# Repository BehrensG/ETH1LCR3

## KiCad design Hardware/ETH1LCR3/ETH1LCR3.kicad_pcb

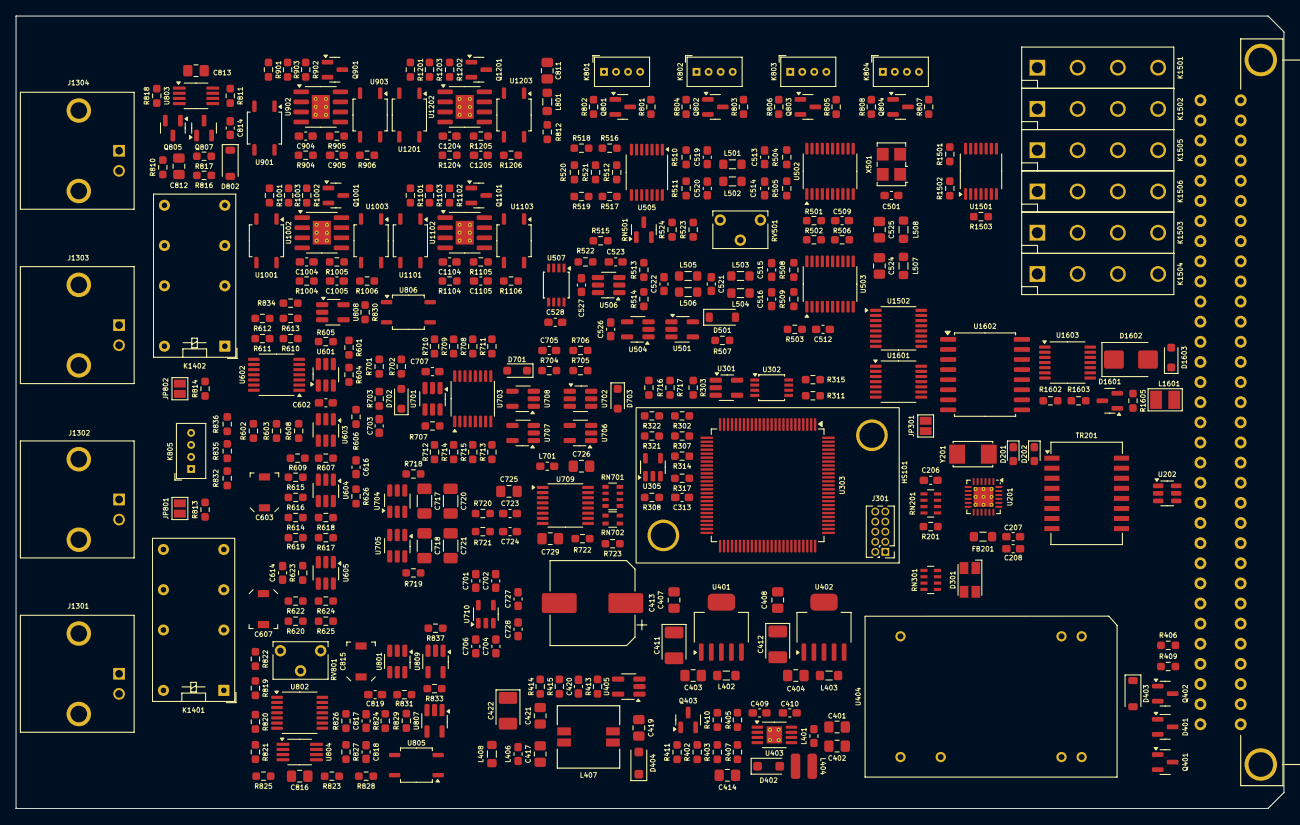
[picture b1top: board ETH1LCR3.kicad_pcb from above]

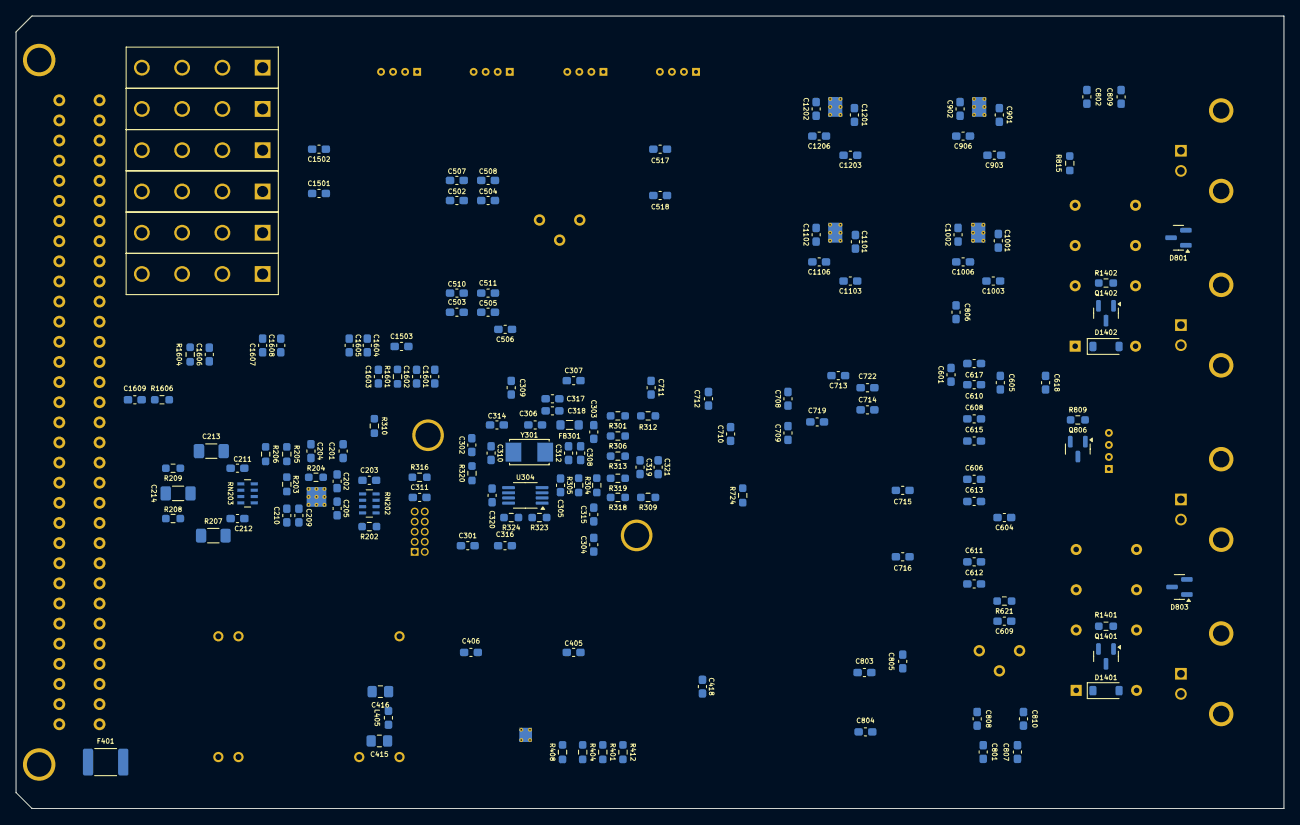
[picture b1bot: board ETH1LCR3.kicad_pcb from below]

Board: 4 copper layers, 160.0 x 100.0 mm, 534 parts (158 on the bottom side), 378 nets, no tracks yet.

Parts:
C201, C204, C310, C312: 8p; C_0603_1608Metric_Pad1.08x0.95mm_HandSolder
C202, C208, C209, C210, C211, C212, C301, C302, C303, C304, C306, C307, C308, C309, C311, C313, C318, C320, C321, C410, C501, C502, C503, C506, C507, C508, C509, C510, C511, C512, C517, C518, C526, C527, C528, C605, C606, C608, C610, C611, C612, C613, C615, C617, C618, C701, C704, C705, C708, C709, C710, C712, C713, C714, C715, C716, C719, C722, C728, C801, C802, C803, C804, C805, C806, C807, C808, C809, C810, C901, C902, C1001, C1002, C1101, C1102, C1201, C1202, C1501, C1502, C1601, C1603, C1604, C1606, C1608: 0.1u; C_0603_1608Metric_Pad1.08x0.95mm_HandSolder
C203: 470p; C_0603_1608Metric_Pad1.08x0.95mm_HandSolder
C205, C206, C207, C314, C319, C418, C702, C703, C706, C727, C1503, C1602, C1605, C1607: 1u; C_0603_1608Metric_Pad1.08x0.95mm_HandSolder
C213, C214: 1n/1kV; C_1206_3216Metric_Pad1.33x1.80mm_HandSolder
C305: 100n; C_0603_1608Metric_Pad1.08x0.95mm_HandSolder
C315, C316: 2u2; C_0603_1608Metric_Pad1.08x0.95mm_HandSolder
C317: 10u; C_0603_1608Metric_Pad1.08x0.95mm_HandSolder
C401, C414, C415, C417, C421, C524, C525, C725, C726, C729, C812, C813, C816: 4u7; C_0805_2012Metric_Pad1.18x1.45mm_HandSolder
C402, C403, C404, C407, C408, C416: 2u2; C_0805_2012Metric_Pad1.18x1.45mm_HandSolder
C405, C406, C504, C505, C814, C819: 10n; C_0603_1608Metric_Pad1.08x0.95mm_HandSolder
C409: 270p; C_0603_1608Metric_Pad1.08x0.95mm_HandSolder
C411, C412, C422: 33u/12V; CP_EIA-3528-21_Kemet-B_Pad1.50x2.35mm_HandSolder
C413: 470u/12V; CP_Elec_10x10.5
C419: 1u; C_0805_2012Metric_Pad1.18x1.45mm_HandSolder
C420: 1n; C_0603_1608Metric_Pad1.08x0.95mm_HandSolder
C513, C514, C519, C520: 220p; C_0603_1608Metric_Pad1.08x0.95mm_HandSolder
C515, C516, C616: 82p; C_0603_1608Metric_Pad1.08x0.95mm_HandSolder
C521: 68p; C_0603_1608Metric_Pad1.08x0.95mm_HandSolder
C522, C601, C1609: 47p; C_0603_1608Metric_Pad1.08x0.95mm_HandSolder
C523, C604, C906, C1006, C1106, C1206: 1p5; C_0603_1608Metric_Pad1.08x0.95mm_HandSolder
C602, C903, C1003, C1103: DNP; C_0603_1608Metric_Pad1.08x0.95mm_HandSolder
C603, C607: JZ200; C_Trimmer_Voltronics_JZ
C609: 240p; C_0603_1608Metric_Pad1.08x0.95mm_HandSolder
C614, C707, C905, C1005, C1105, C1205: 22p; C_0603_1608Metric_Pad1.08x0.95mm_HandSolder
C711: 100p; C_0603_1608Metric_Pad1.08x0.95mm_HandSolder
C717, C718, C720, C721: 100n/C0G; C_1206_3216Metric_Pad1.33x1.80mm_HandSolder
C723, C724: 15p/C0G; C_0603_1608Metric_Pad1.08x0.95mm_HandSolder
C811: DNP; C_0805_2012Metric_Pad1.18x1.45mm_HandSolder
C815: JZ100; C_Trimmer_Voltronics_JZ
C817: 6p8; C_0603_1608Metric_Pad1.08x0.95mm_HandSolder
C818: 180p; C_0603_1608Metric_Pad1.08x0.95mm_HandSolder
C904, C1004, C1104, C1204: 3p9; C_0603_1608Metric_Pad1.08x0.95mm_HandSolder
C1203: 1p; C_0603_1608Metric_Pad1.08x0.95mm_HandSolder
D201: YELLOW; LED_0603_1608Metric_Pad1.05x0.95mm_HandSolder
D202: GREEN; LED_0603_1608Metric_Pad1.05x0.95mm_HandSolder
D301: ASMB-MTB1-0B3A2; LED_Avago_PLCC4_3.2x2.8mm_CW
D401: BZX84C10LT1G; SOT-23
D402, D404: MBR0520; D_SOD-123F
D403, D501, D802, D1401, D1402: 1N4148W; D_SOD-123
D701, D702, D703: NSVRB751V40T1G; D_SOD-323_HandSoldering
D801, D803: BAV199; SOT-23
D1601: BAV99; SOT-23
D1602: SMBJ5.0A; D_SMB
D1603: SD36C-01FTG; D_SOD-323_HandSoldering
F401: 1812L075/33DR; Fuse_1812_4532Metric_Pad1.30x3.40mm_HandSolder
FB201, FB301: 742792031; L_0805_2012Metric_Pad1.05x1.20mm_HandSolder
HS101: Heatsink; 960-19-12-S-AB-0
J301: 20021111-00010T4LF; PinHeader_2x05_P1.27mm_Vertical
J1301, J1302, J1303, J1304: 5227161-1; TE_5227161-1
J1501: DIN41612_02x32_AC; Socket_DIN41612-CaseC1-AC-Male-64Pin-2rows
JP301, JP801, JP802: Open; SolderJumper-2_P1.3mm_Open_Pad1.0x1.5mm
K801, K802, K803, K804, K805: UMS05-1A80-75D; Relay_StandexMeder_UMS
K1401, K1402: G5V-2-DC5; Relay_DPDT_Omron_G5V-2
K1501, K1502, K1503, K1504, K1505, K1506: HE3621A0510; HE360_x-5050462-8
L401, L405, L406, L701: MLZ1608DR47DT; L_0603_1608Metric_Pad1.05x0.95mm_HandSolder
L402, L403, L408, L507, L508: MLZ2012M100WT; L_0805_2012Metric_Pad1.05x1.20mm_HandSolder
L404: SRN3010TA-2R2M; SRN3010TA
L407: DRQ73-220-R; DRQ73
L501, L502, L503, L504, L505, L506: MLZ2012M330WT; L_0805_2012Metric_Pad1.05x1.20mm_HandSolder
L801: DNP; L_0805_2012Metric_Pad1.05x1.20mm_HandSolder
L1601: CW252016-R33G; CW252016
Q401: SI5618A; SOT-23
Q402, Q801, Q802, Q803, Q804, Q806, Q1401, Q1402: MMBT3904; SOT-23
Q403, Q901, Q1001, Q1101, Q1201: BSS123; SOT-23
Q805, Q807: BFR106; SOT-23
R201, R204, R310, R316, R403, R404, R407, R414, R802, R804, R806, R808, R809, R902, R1002, R1102, R1202, R1401, R1402, R1601: 10k; R_0603_1608Metric_Pad0.98x0.95mm_HandSolder
R202, R315, R704: 1k5; R_0603_1608Metric_Pad0.98x0.95mm_HandSolder
R203: 12k1; R_0603_1608Metric_Pad0.98x0.95mm_HandSolder
R205, R206, R901, R1001, R1101, R1201: 560; R_0603_1608Metric_Pad0.98x0.95mm_HandSolder
R207: 1M/1kV; R_1206_3216Metric_Pad1.30x1.75mm_HandSolder
R208, R209: 75/1%; R_0603_1608Metric_Pad0.98x0.95mm_HandSolder
R301, R705, R720, R721: 3k; R_0603_1608Metric_Pad0.98x0.95mm_HandSolder
R302, R606, R707: 2k; R_0603_1608Metric_Pad0.98x0.95mm_HandSolder
R303, R401, R402, R412, R522, R602, R603, R614, R626, R722, R833, R834, R837, R905, R906, R1005, R1006, R1105, R1106, R1205, R1206, R1501, R1502: 51; R_0603_1608Metric_Pad0.98x0.95mm_HandSolder
R304, R309: 110k; R_0603_1608Metric_Pad0.98x0.95mm_HandSolder
R305, R308, R406, R409, R411, R523, R723, R724, R813, R814, R818, R823, R824, R827, R831: 100k; R_0603_1608Metric_Pad0.98x0.95mm_HandSolder
R306: 3k6; R_0603_1608Metric_Pad0.98x0.95mm_HandSolder
R307, R716, R717: 1k6; R_0603_1608Metric_Pad0.98x0.95mm_HandSolder
R311, R507, R811, R829, R830, R1503, R1604: 1k; R_0603_1608Metric_Pad0.98x0.95mm_HandSolder
R312, R1605: 47; R_0603_1608Metric_Pad0.98x0.95mm_HandSolder
R313: 56k; R_0603_1608Metric_Pad0.98x0.95mm_HandSolder
R314: 160k; R_0603_1608Metric_Pad0.98x0.95mm_HandSolder
R317, R318, R323, R324, R501, R506, R512: 4k7; R_0603_1608Metric_Pad0.98x0.95mm_HandSolder
R319, R320, R321, R322: 0; R_0603_1608Metric_Pad0.98x0.95mm_HandSolder
R405: 27k; R_0603_1608Metric_Pad0.98x0.95mm_HandSolder
R408: 2k4; R_0603_1608Metric_Pad0.98x0.95mm_HandSolder
R410, R706: 12k; R_0603_1608Metric_Pad0.98x0.95mm_HandSolder
R413, R415: 30k; R_0603_1608Metric_Pad0.98x0.95mm_HandSolder
R502, R516, R517, R518, R519, R520, R521: 3k9; R_0603_1608Metric_Pad0.98x0.95mm_HandSolder
R503: 6k8; R_0603_1608Metric_Pad0.98x0.95mm_HandSolder
R504, R505, R510, R511: 390; R_0603_1608Metric_Pad0.98x0.95mm_HandSolder
R508, R509, R513, R514: 620; R_0603_1608Metric_Pad0.98x0.95mm_HandSolder
R515: 7k5; R_0603_1608Metric_Pad0.98x0.95mm_HandSolder
R524: 300; R_0603_1608Metric_Pad0.98x0.95mm_HandSolder
R601: 47k; R_0603_1608Metric_Pad0.98x0.95mm_HandSolder
R604, R609, R619, R625, R703, R810: 510; R_0603_1608Metric_Pad0.98x0.95mm_HandSolder
R605: 10; R_0603_1608Metric_Pad0.98x0.95mm_HandSolder
R607, R617, R624: 1k3; R_0603_1608Metric_Pad0.98x0.95mm_HandSolder
R608: 620/0.1%; R_0603_1608Metric_Pad0.98x0.95mm_HandSolder
R610: 150/0.1%; R_0603_1608Metric_Pad0.98x0.95mm_HandSolder
R611: 91/0.1%; R_0603_1608Metric_Pad0.98x0.95mm_HandSolder
R612, R613: 30/0.1%; R_0603_1608Metric_Pad0.98x0.95mm_HandSolder
R615: 1k2; R_0603_1608Metric_Pad0.98x0.95mm_HandSolder
R616: 100/0.1%; R_0603_1608Metric_Pad0.98x0.95mm_HandSolder
R618: 200/0.1%; R_0603_1608Metric_Pad0.98x0.95mm_HandSolder
R620: 75; R_0603_1608Metric_Pad0.98x0.95mm_HandSolder
R621, R812: DNP; R_0603_1608Metric_Pad0.98x0.95mm_HandSolder
R622: 43/0.1%; R_0603_1608Metric_Pad0.98x0.95mm_HandSolder
R623: 390/0.1%; R_0603_1608Metric_Pad0.98x0.95mm_HandSolder
R701: 30k/.1%; R_0603_1608Metric_Pad0.98x0.95mm_HandSolder
R702: 120k/.1%; R_0603_1608Metric_Pad0.98x0.95mm_HandSolder
R708: 10/.1%; R_0603_1608Metric_Pad0.98x0.95mm_HandSolder
R709: 51/.1%; R_0603_1608Metric_Pad0.98x0.95mm_HandSolder
R710: 240/.1%; R_0603_1608Metric_Pad0.98x0.95mm_HandSolder
R711, R819, R820: 1k/.1%; R_0603_1608Metric_Pad0.98x0.95mm_HandSolder
R712: 5k1/.1%; R_0603_1608Metric_Pad0.98x0.95mm_HandSolder
R713: 20k/.1%; R_0603_1608Metric_Pad0.98x0.95mm_HandSolder
R714: 51k/.1%; R_0603_1608Metric_Pad0.98x0.95mm_HandSolder
R715: 75k/.1%; R_0603_1608Metric_Pad0.98x0.95mm_HandSolder
R718, R719: 100/.05%; R_0603_1608Metric_Pad0.98x0.95mm_HandSolder
R801, R904: 100/.01%; R_0603_1608Metric_Pad0.98x0.95mm_HandSolder
R803, R1004: 1k/.01%; R_0603_1608Metric_Pad0.98x0.95mm_HandSolder
R805, R1104: 10k/.01%; R_0603_1608Metric_Pad0.98x0.95mm_HandSolder
R807, R1204: 100k/.01%; R_0603_1608Metric_Pad0.98x0.95mm_HandSolder
R815: 200k; R_0603_1608Metric_Pad0.98x0.95mm_HandSolder
R816, R817, R1603: 100; R_0603_1608Metric_Pad0.98x0.95mm_HandSolder
R821, R822, R825, R826: 2k/.1%; R_0603_1608Metric_Pad0.98x0.95mm_HandSolder
R828: 240; R_0603_1608Metric_Pad0.98x0.95mm_HandSolder
R832, R835, R836: 33; R_0603_1608Metric_Pad0.98x0.95mm_HandSolder
R903, R1003, R1103, R1203: 20k; R_0603_1608Metric_Pad0.98x0.95mm_HandSolder
R1602: 14k7; R_0603_1608Metric_Pad0.98x0.95mm_HandSolder
R1606: 51R1; R_0603_1608Metric_Pad0.98x0.95mm_HandSolder
RN201: EXB-V8V330JV; R_Array_Concave_4x0603
RN202: EXB-V8V103JV; R_Array_Concave_4x0603
RN203: EXB-38V510JV; R_Array_Concave_4x0603
RN301: EXB-V8V102JV; R_Array_Concave_4x0603
RN501: MPMT2001AT; SOT-23
RN701: 51; R_Array_Convex_4x0603
RN702: 51; R_Array_Convex_2x0603
RV501: 3266W-1-103LF; Potentiometer_Bourns_3266W_Vertical
RV801: 3266W-1-500LF; Potentiometer_Bourns_3266W_Vertical
TR201: Wuerth_749013011A; Transformer_Ethernet_Wuerth_749013011A
U201: LAN8742A; VQFN-24-1EP_4x4mm_P0.5mm_EP2.5x2.5mm_ThermalVias
U202: SRV05-4; SOT-23-6
U301, U504, U706, U707, U708, U807, U808, U809: SN74LV1T34DBV; SOT-23-5_HandSoldering
U302, U507: 74LVC1G74DP; TSSOP-8_3x3mm_P0.65mm
U303: STM32H743VITx; LQFP-100_14x14mm_P0.5mm
U304: 24LC08B-E/MS; MSOP-8_3x3mm_P0.65mm
U305: REF2033; SOT-23-5
U401: REG103GA-5; SOT-223-6
U402: REG103GA-3.3; SOT-223-6
U403: LT1946A; MSOP-8-1EP_3x3mm_P0.65mm_EP1.95x2.15mm_ThermalVias
U404: TEL5-2411; CONV_TEL_5-2411
U405: LT1611; SOT-23-5_HandSoldering
U501: SN74LVC1G04DBV; SOT-23-5_HandSoldering
U502, U503: AD9834; TSSOP-20_4.4x6.5mm_P0.65mm
U505, U802, U1501: LMH6644MT; TSSOP-14_4.4x5mm_P0.65mm
U506, U702: TLV3501AIDBV; SOT-23-6_Handsoldering
U601, U701: LMH6618MKE; SOT-23-6_Handsoldering
U602: ADG1604BRUZ; TSSOP-14_4.4x5mm_P0.65mm
U603, U604, U605: LMH6720MF; SOT-23-6_Handsoldering
U703: 74HCT4051PW; TSSOP-16_4.4x5mm_P0.65mm
U704, U705: SN74LVC1G3157DB; SOT-23-6_Handsoldering
U709: ADS1246IPWR; TSSOP-16_4.4x5mm_P0.65mm
U710: REF2025; SOT-23-5
U801: 74LVC1G3157DB; SOT-23-6_Handsoldering
U803, U804: OPA727AIDG; MSOP-8_3x3mm_P0.65mm
U805, U806, U901, U903, U1001, U1003, U1101, U1103, U1201, U1203: AQY221R2S; SOP-4_3.8x4.1mm_P2.54mm
U902, U1002, U1102, U1202: AD8099ARDZ; SOIC-8-1EP_3.9x4.9mm_P1.27mm_EP2.29x3mm_ThermalVias
U1502: ULN2003A; TSSOP-16_4.4x5mm_P0.65mm
U1601: TXB0104PW; TSSOP-14_4.4x5mm_P0.65mm
U1602: ADuM5402; SOIC-16W_7.5x10.3mm_P1.27mm
U1603: 74AC125; TSSOP-14_4.4x5mm_P0.65mm
X501: SG-5032CAN; Oscillator_SMD_SeikoEpson_SG8002LB-4Pin_5.0x3.2mm
Y201: NX5032GA-25; NX5032GA
Y301: NX5032GA-16; NX5032GA

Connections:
+1V25: C704.1, C706.1, U710.1 (Vbias)
+2V5: C701.1, C702.1, C725.1, R312.1, R322.2, R701.1, R705.1, U709.5 (REFP), U710.5 (Vref)
+3.3V: C202.1, C205.1, C301.1, C302.1, C303.1, C304.1, C306.1, C314.1, C320.2, C408.1, C412.1, C1601.1, C1602.1, D301.4 (A), FB201.2, FB301.2, J301.1, L507.2, L508.2, L701.2, R202.1, R310.2, R316.1, R323.1, R324.1, R723.2, R724.2, R1601.1, RN202.5 (R4.2), RN202.6 (R3.2), RN202.7 (R2.2), RN202.8 (R1.2), U201.9 (VDDIO), U303.6 (VBAT), U303.11 (VDD), U303.27 (VDD), U303.50 (VDD), U303.75 (VDD), U303.100 (VDD), U304.8 (VCC), U402.2 (VOUT), U1601.1 (VCCA)
+3.3VADC: R321.2, U305.5 (Vref)
+5V: C307.1, C309.1, C319.1, C321.1, C407.1, C411.1, C413.1, C526.1, C527.1, C528.1, C612.1, C613.1, C615.1, C617.1, C618.1, C708.1, C709.1, C710.1, C712.1, C713.1, C714.1, C715.1, C716.1, C727.1, C728.1, C801.1, C802.1, C803.1, C804.1, C805.1, C806.1, C902.1, C1002.1, C1102.1, C1202.1, C1603.1, C1604.1, C1605.1, D702.1 (K), K801.1, K802.1, K803.1, K804.1, K805.1, R301.1, R305.1, R308.1, R606.2, R707.2, R722.1, R829.1, R830.1, R901.1, R903.1, R1001.1, R1003.1, R1101.1, R1103.1, R1201.1, R1203.1, RV501.1, U301.5 (VCC), U302.6 (~CLR), U302.7 (~PRE), U302.8 (VCC), U305.3 (EN), U305.4 (IN), U401.2 (VOUT), U504.5 (VCC), U506.4 (V+), U507.7 (~PRE), U507.8 (VCC), U601.6 (V+), U602.2 (EN), U602.12 (VDD), U603.6 (V+), U604.6 (V+), U605.6 (V+), U701.6 (V+), U702.4 (V+), U703.16 (VCC), U704.5 (VCC), U705.5 (VCC), U706.5 (VCC), U707.5 (VCC), U708.5 (VCC), U710.3 (EN), U710.4 (IN), U801.5 (VCC), U803.7 (V+), U804.7 (V+), U807.5 (VCC), U808.5 (VCC), U809.5 (VCC), U902.7 (V+), U1002.7 (V+), U1102.7 (V+), U1202.7 (V+), U1601.14 (VCCB), U1602.1 (VDD1)
+5VL: C1606.1, C1607.1, C1608.1, R1604.1, U1602.10 (VSEL), U1602.16 (VISO), U1603.14 (VCC)
+5VP: C401.1, C416.1, C1503.1, D1401.1 (K), D1402.1 (K), K1401.1, K1402.1, K1501.2, K1502.2, K1503.2, K1504.2, K1505.2, K1506.2, L401.1, L403.1, L405.2, L406.1, U1502.9 (COM)
+24V: F401.1, J1501.a31, J1501.a32, J1501.c31, J1501.c32
-5V: C518.2, C605.1, C606.1, C608.1, C610.1, C611.1, C719.1, C722.1, C807.1, C808.1, C809.1, C812.2, C901.1, C904.2, C1001.1, C1004.2, C1101.1, C1104.2, C1201.1, C1204.2, C1502.1, D803.1 (K), L408.2, R309.2, R314.2, R810.2, R816.2, R817.2, RV501.3, U505.11 (V-), U601.2 (V-), U602.3 (VSS), U603.2 (V-), U604.2 (V-), U605.2 (V-), U701.2 (V-), U703.7 (VEE), U802.11 (V-), U803.4 (V-), U804.4 (V-), U902.4 (V-), U1002.4 (V-), U1102.4 (V-), U1202.4 (V-), U1501.11 (V-)
/Connector/A: J1501.a2, J1501.c2, K1501.4
/Connector/B: J1501.a3, J1501.c3, K1502.4
/Connector/C: J1501.a4, J1501.c4, K1505.4
/Connector/CXN_REL1: U303.87 (PD6), U1502.1 (I1)
/Connector/CXN_REL2: U303.88 (PD7), U1502.2 (I2)
/Connector/CXN_REL3: U303.89 (PB3), U1502.3 (I3)
/Connector/CXN_REL4: U303.90 (PB4), U1502.4 (I4)
/Connector/CXN_REL5: U303.95 (PB8), U1502.5 (I5)
/Connector/CXN_REL6: U303.96 (PB9), U1502.6 (I6)
/Connector/D: J1501.a5, J1501.c5, K1506.4
/Connector/E: J1501.a6, J1501.c6, K1503.4
/Connector/EXT_TRIG: C1609.1, D1603.1 (A1), J1501.a16, L1601.1
/Connector/F: J1501.a7, J1501.c7, K1504.4
/Connector/HD_REAR: K1401.8, K1501.1
/Connector/HS_REAR: K1401.9, K1504.1
/Connector/LD_REAR: K1402.9, K1502.1
/Connector/LS_REAR: K1402.8, K1503.1
/Connector/RX+: J1501.a20, TR201.11 (RX+), U202.3 (IO2)
/Connector/RX-: J1501.a21, TR201.9 (RX-), U202.4 (IO3)
/Connector/TX+: J1501.c20, TR201.16 (TX+), U202.6 (IO4)
/Connector/TX-: J1501.c21, TR201.14 (TX-), U202.1 (IO1)
/DDS/27MHz: U502.8 (MCLK), U503.8 (MCLK), X501.3 (OUT)
/DDS/DAC0_OUT: R524.2, U303.28 (PA4)
/DDS/DAC1_OUT: R506.1, U303.29 (PA5)
/DDS/DC_BIAS_VOLTAGE: R521.2, RN501.1, U505.8, U801.1
/DDS/DDS_RESET: U303.45 (PE15), U501.2, U504.2 (A)
/DDS/DDS_SCLK: U303.42 (PE12), U502.14 (SCLK), U503.14 (SCLK)
/DDS/DDS_SDATA: U303.44 (PE14), U502.13 (SDATA), U503.13 (SDATA)
/DDS/DDS_~FSYNC1: U303.40 (PE10), U502.15 (~FSYNC)
/DDS/DDS_~FSYNC2: U303.41 (PE11), U503.15 (~FSYNC)
/DDS/PHI_OUT: U302.1 (CLK), U507.5 (Q), U704.6, U705.6
/DDS/SINE: R520.2, R836.2, U505.7
/Ethernet/ETH_RXN: RN203.1 (R1.1), TR201.8 (RD-), U201.22 (RXN)
/Ethernet/ETH_RXP: RN203.2 (R2.1), TR201.6 (RD+), U201.23 (RXP)
/Ethernet/ETH_TXN: RN203.3 (R3.1), TR201.3 (TD-), U201.20 (TXN)
/Ethernet/ETH_TXP: RN203.4 (R4.1), TR201.1 (TD+), U201.21 (TXP)
/Ethernet/LED1: D202.2 (A), U201.3 (LED1/REGOFF)
/Ethernet/LED2: D201.2 (A), R204.1, U201.2 (LED2/~INTSEL)
/Ethernet/MODE0: RN201.8 (R1.2), RN202.1 (R1.1), U201.8 (RXD0/MODE0)
/Ethernet/MODE1: RN201.7 (R2.2), RN202.2 (R2.1), U201.7 (RXD1/MODE1)
/Ethernet/MODE2: RN201.6 (R3.2), RN202.3 (R3.1), U201.11 (CRS_DV/MODE2)
/Ethernet/REFCLK0: RN201.5 (R4.2), RN202.4 (R4.1), U201.14 (~INT/REFCLKO)
/Ethernet/REF_CLK: RN201.4 (R4.1), U303.23 (PA1)
/Ethernet/RMII_CRS_DV: RN201.3 (R3.1), U303.31 (PA7)
/Ethernet/RMII_MDC: U201.13 (MDC), U303.16 (PC1)
/Ethernet/RMII_MDIO: R202.2, U201.12 (MDIO), U303.24 (PA2)
/Ethernet/RMII_RXD0: RN201.1 (R1.1), U303.32 (PC4)
/Ethernet/RMII_RXD1: RN201.2 (R2.1), U303.33 (PC5)
/Ethernet/RMII_TXD0: U201.17 (TXD0), U303.51 (PB12)
/Ethernet/RMII_TXD1: U201.18 (TXD1), U303.52 (PB13)
/Ethernet/RMII_TXEN: U201.16 (TXEN), U303.47 (PB11)
/Front/HD_FRONT: J1301.1 (In), K1401.6
/Front/HS_FRONT: J1302.1 (In), K1401.11
/Front/LD_FRONT: J1304.1 (In), K1402.11
/Front/LS_FRONT: J1303.1 (In), K1402.6
/Frontend/CALIB_1K: R804.2, U303.84 (PD3)
/Frontend/CALIB_10K: R806.2, U303.85 (PD4)
/Frontend/CALIB_100: R802.2, U303.83 (PD2)
/Frontend/CALIB_100K: R808.2, U303.86 (PD5)
/Frontend/DC_BIAS_U-I: R837.2, U303.3 (PE4)
/Frontend/FE_SW5: R833.2, U303.61 (PD14)
/Frontend/FE_SW6: R834.2, U303.62 (PD15)
/Frontend/FE_V_SHORT: R809.1, U303.2 (PE3)
/Frontend/HD: JP801.1 (A), K1401.4, R801.1, R803.1, R805.1, R807.1, R813.1, R832.1
/Frontend/HS: D803.3 (K), JP801.2 (B), K805.3, K1401.13, R813.2, U802.3 (+)
/Frontend/IV 1k/SW2: R1002.1, U303.58 (PD11), U1003.2
/Frontend/IV 10k/SW3: R1102.1, U303.59 (PD12), U1103.2
/Frontend/IV 100/IV_100_OUT: R818.2, U806.3, U903.4, U1003.4, U1103.4, U1203.4
/Frontend/IV 100/SW1: R902.1, U303.57 (PD10), U903.2
/Frontend/IV 100k/SW4: R1202.1, U303.60 (PD13), U1203.2
/Frontend/I_VOLTAGE: C814.2, Q807.2 (E), R304.1, R816.1, R817.1
/Frontend/LD: C811.1, D801.3 (K), D802.2 (A), JP802.2 (B), K801.4, K802.4, K803.4, K804.4, K1402.13, R814.2, R815.1, U901.3, U1001.3, U1101.3, U1201.3
/Frontend/LS: JP802.1 (A), K805.4, K1402.4, R814.1, U802.5 (+)
/Frontend/PGA_IN: C601.1, R601.1, R604.1, U805.4, U806.4
/MCU/ADC_+5V: R301.2, R302.1, U303.25 (PA3)
/MCU/ADC_-5V: C308.2, R313.2, R314.1, U303.30 (PA6)
/MCU/ADC_IV_1: C305.1, R304.2, R305.2, U303.34 (PB0)
/MCU/ADC_IV_2: C305.2, R308.2, R309.1, U303.35 (PB1)
/MCU/ADC_VBOOST: R306.2, R307.1, U303.22 (PA0)
/MCU/ADS_DIN: RN701.7 (R2.2), U303.80 (PC12)
/MCU/ADS_DOUT: RN701.6 (R3.2), U303.79 (PC11)
/MCU/ADS_SCLK: RN701.8 (R1.2), U303.78 (PC10)
/MCU/ADS_START: RN702.1 (R1.1), U303.82 (PD1)
/MCU/ADS_~CS: RN702.2 (R2.1), U303.77 (PA15)
/MCU/ADS_~DRDY: RN701.5 (R4.2), U303.81 (PD0)
/MCU/EEPROM_nWP: U303.91 (PB5), U304.7 (WP)
/MCU/EN_BOOST: R402.1, U303.54 (PB15)
/MCU/I2C1_SCL: R324.2, U303.92 (PB6), U304.6 (SCL)
/MCU/I2C1_SDA: R323.2, U303.93 (PB7), U304.5 (SDA)
/MCU/INPUT_COMP: R716.2, R717.2, U303.39 (PE9)
/MCU/LED_BLUE: RN301.3 (R3.1), U303.63 (PC6)
/MCU/LED_GREEN: RN301.2 (R2.1), U303.65 (PC8)
/MCU/LED_RED: RN301.1 (R1.1), U303.66 (PC9)
/MCU/MAX_BOOST: R412.2, U303.53 (PB14)
/MCU/MCU_DEF: JP301.1 (A), R310.1, U303.1 (PE2)
/MCU/NRST: C311.1, J301.10, R316.2, U201.15 (~RST), U303.14 (NRST)
/MCU/PGA_A0: R603.1, U303.70 (PA11)
/MCU/PGA_A1: R607.2, R609.1, U303.71 (PA12)
/MCU/PGA_G1: R602.1, U303.67 (PA8)
/MCU/PGA_G3: R617.2, R619.1, U303.68 (PA9)
/MCU/PGA_G10: R624.2, R625.1, U303.69 (PA10)
/MCU/PSD_RC_A: U303.7 (PC13), U706.2 (A)
/MCU/PSD_RC_B: U303.8 (PC14), U707.2 (A)
/MCU/PSD_RC_C: U303.9 (PC15), U708.2 (A)
/MCU/SELECT_RELAY: R1401.1, R1402.1, U303.4 (PE5)
/MCU/SYNCH_CDE: R303.1, U303.97 (PE0)
/MCU/SYNCH_OUT: R311.2, R315.2, U303.98 (PE1)
/MCU/TCK_SWCLK: J301.4, U303.76 (PA14)
/MCU/TMS_SWDIO: J301.2, U303.72 (PA13)
/MCU/TRIG_EN: U303.15 (PC0), U1601.2 (A1)
/MCU/TRIG_IN: U303.18 (PC3_C), U1601.4 (A3)
/MCU/TRIG_OUT: U303.17 (PC2_C), U1601.3 (A2)
/PGA/PGA_OUT: C614.1, C616.1, C703.2, R608.1, R618.1, R623.1, R704.1, U603.1, U604.1, U605.1
/Trigger/EXT_TRIG_SIGN: R1602.1, U1602.12 (VIC), U1603.3 (O)
/Trigger/TRIG_OUT_EN: U1602.14 (VOA), U1603.4 (EN), U1603.10 (EN), U1603.13 (EN)
/Trigger/TRIG_OUT_SIGN: U1602.13 (VOB), U1603.5 (D), U1603.9 (D), U1603.12 (D)
AVDD_DDS: C504.1, C505.1, C508.1, C511.1, C524.1, L507.1, U502.4 (AVDD), U503.4 (AVDD)
DVDD_DDS: C501.1, C507.1, C510.1, C525.1, L508.1, U501.5 (VCC), U502.5 (DVDD), U503.5 (DVDD), X501.4 (VCC)
Earth: C213.1, C214.2, J1501.a18, J1501.a22, J1501.c18, J1501.c22, R207.1
GND: C201.2, C202.2, C203.2, C204.2, C205.2, C206.2, C207.2, C208.2, C209.2, C210.2, C211.2, C212.2, C213.2, C301.2, C302.2, C303.2, C304.2, C306.2, C307.2, C308.1, C309.2, C310.2, C311.2, C312.2, C313.2, C314.2, C315.2, C316.2, C317.2, C318.2, C319.2, C320.1, C321.2, C401.2, C402.2, C403.2, C404.2, C405.2, C406.2, C407.2, C408.2, C409.2, C410.2, C411.2, C412.2, C413.2, C414.2, C415.2, C416.2, C417.2, C418.2, C421.2, C422.1, C501.2, C502.1, C503.1, C506.2, C507.2, C508.2, C509.2, C510.2, C511.2, C512.2, C513.2, C514.1, C515.2, C516.1, C517.1, C518.1, C519.2, C520.1, C524.2, C525.2, C526.2, C527.2, C528.2, C601.2, C603.2, C604.2, C605.2, C606.2, C607.2, C608.2, C609.2, C610.2, C611.2, C612.2, C613.2, C615.2, C617.2, C618.2, C701.2, C702.2, C704.2, C705.2, C706.2, C707.2, C708.2, C709.2, C710.2, C711.2, C712.2, C713.2, C714.2, C715.2, C716.2, C717.2, C718.2, C719.2, C720.2, C721.2, C722.2, C723.1, C724.2, C725.2, C726.1, C727.2, C728.2, C729.2, C801.2, C802.2, C803.2, C804.2, C805.2, C806.2, C807.2, C808.2, C809.2, C810.2, C819.2, C901.2, C902.2, C1001.2, C1002.2, C1101.2, C1102.2, C1201.2, C1202.2, C1501.2, C1502.2, C1503.2, C1601.2, C1602.2, C1603.2, C1604.2, C1605.2, D404.1 (K), D701.2 (A), D801.1 (K), D801.2 (A), J301.3, J301.5, J1301.2 (Ext), J1302.2 (Ext), J1303.2 (Ext), J1304.2 (Ext), JP301.2 (B), K1505.1, Q403.2 (S), Q801.2 (E), Q802.2 (E), Q803.2 (E), Q804.2 (E), Q806.2 (E), Q901.2 (S), Q1001.2 (S), Q1101.2 (S), Q1201.2 (S), Q1401.2 (E), Q1402.2 (E), R201.1, R203.1, R204.2, R205.2, R206.2, R207.2, R302.2, R307.2, R315.1, R318.1, R319.1, R320.2, R403.2, R408.2, R411.2, R414.2, R502.1, R503.2, R504.2, R505.1, R508.2, R509.1, R510.2, R511.1, R513.2, R514.1, R601.2, R609.2, R613.2, R615.2, R616.2, R619.2, R621.2, R622.2, R625.2, R626.2, R702.2, R706.2, R717.1, R812.2, R828.2, R831.2, R906.2, R1006.2, R1106.2, R1206.2, RN501.2, U201.25 (VSS), U301.3 (GND), U302.4 (GND), U303.10 (VSS), U303.19 (VSSA), U303.26 (VSS), U303.49 (VSS), U303.74 (VSS), U303.99 (VSS), U304.1 (A0), U304.2 (A1), U304.3 (A2), U304.4 (GND), U305.2 (GND), U401.3 (GND), U401.6 (GND), U402.3 (GND), U402.6 (GND), U403.4 (GND), U403.7 (COMP), U403.9 (GND), U404.16 (VOUT-), U405.2 (GND), U501.3 (GND), U502.7 (DGND), U502.9 (FSELECT), U502.10 (PSELECT), U502.12 (SLEEP), U502.18 (AGND), U503.7 (DGND), U503.9 (FSELECT), U503.10 (PSELECT), U503.12 (SLEEP), U503.18 (AGND), U504.3 (GND), U506.2 (V-), U506.6 (SHDN), U507.4 (GND), U602.13 (GND), U702.2 (V-), U702.6 (SHDN), U703.6 (~E), U703.8 (GND), U704.2 (GND), U705.2 (GND), U706.3 (GND), U707.3 (GND), U708.3 (GND), U709.2 (DGND), U709.3 (CLK), U709.6 (REFN), U709.9 (AVSS), U710.2 (GND), U801.2 (GND), U801.3, U803.3 (+), U804.3 (+), U807.3 (GND), U808.3 (GND), U809.3 (GND), U902.3 (+), U902.9 (GND), U1002.3 (+), U1002.9 (GND), U1102.3 (+), U1102.9 (GND), U1202.3 (+), U1202.9 (GND), U1501.5 (+), U1501.10 (+), U1501.12 (+), U1502.8 (GND), U1601.7 (GND), U1602.2 (GND1), U1602.8 (GND1), X501.2 (GND)
GNDPWR: J1501.a27, J1501.a28, J1501.c27, J1501.c28, R406.2, R409.2, U404.2 (VIN-), U404.3 (VIN-)
GNDS: C1606.2, C1607.2, C1608.2, D1601.1 (K), D1602.2 (A), D1603.2 (A2), J1501.c16, R1606.2, U1602.9 (GNDISO), U1602.15 (GNDISO), U1603.1 (EN), U1603.7 (GND)
unnamed: C214.1, R208.2, R209.2
unnamed: C315.1, U303.48 (VCAP)
unnamed: C316.1, U303.73 (VCAP)
unnamed: C409.1, R405.2
unnamed: C420.2, C421.1, C422.2, L407.3, L408.1, R415.2
unnamed: C521.1, L503.2, L505.1
unnamed: C521.2, L504.1, L506.2
unnamed: C523.2, R515.2, R522.1, U506.5
unnamed: C603.1, C604.1, R614.2
unnamed: C607.1, C609.1, R620.2
unnamed: C616.2, R626.1
unnamed: C703.1, R703.2
unnamed: C717.1, C720.1, R718.2
unnamed: C718.1, C721.1, R719.2
unnamed: C811.2, L801.1
unnamed: C813.1, R811.2, U803.6
unnamed: C815.1, R819.2, R822.1, U802.1
unnamed: C816.1, R823.2, U804.6
unnamed: C817.2, C818.1, R824.2, R826.2, R827.2, U802.8, U805.3
unnamed: C818.2, R828.1
unnamed: C904.1, C906.2, R905.2
unnamed: C905.2, R906.1
unnamed: C1004.1, C1006.2, R1005.2
unnamed: C1005.2, R1006.1
unnamed: C1104.1, C1106.2, R1105.2
unnamed: C1105.2, R1106.1
unnamed: C1204.1, C1206.2, R1205.2
unnamed: C1205.2, R1206.1
unnamed: C1609.2, R1606.1
unnamed: D201.1 (K), R205.1
unnamed: D202.1 (K), R206.1
unnamed: D301.3 (BK), RN301.6 (R3.2)
unnamed: D301.2 (GK), RN301.7 (R2.2)
unnamed: D301.1 (RK), RN301.8 (R1.2)
unnamed: D401.1 (A), Q401.1 (G), Q402.3 (C), R406.1
unnamed: D401.3 (K), D403.2 (A), Q401.2 (S), Q402.2 (E), U404.22 (VIN+), U404.23 (VIN+)
unnamed: D402.2 (A), L404.2, U403.5 (SW)
unnamed: D403.1 (K), Q402.1 (B), R409.1
unnamed: C419.2, D404.2 (A), L407.1
unnamed: D501.2 (A), R507.2
unnamed: C522.2, D501.1 (K), L506.1, R514.2, U506.1 (-)
unnamed: D701.1 (K), R704.2, U702.3 (+)
unnamed: D702.2 (A), R701.2, R702.1, R703.1, U701.3 (+)
unnamed: D703.2 (A), U702.5
unnamed: C711.1, D703.1 (K), R716.1
unnamed: C814.1, D802.1 (K), Q807.3 (C), R815.2
unnamed: D1401.2 (A), K1401.16, Q1401.3 (C)
unnamed: D1402.2 (A), K1402.16, Q1402.3 (C)
unnamed: D1601.2 (A), D1602.1 (K), R1604.2
unnamed: K801.3, R801.2
unnamed: K802.3, R803.2
unnamed: K803.3, R805.2
unnamed: K804.3, R807.2
unnamed: K1506.1, R1503.2
unnamed: L801.2, R812.1
unnamed: L1601.2, R1605.2
unnamed: F401.2, Q401.3 (D)
unnamed: Q403.3 (D), R410.2
unnamed: Q403.1 (G), R411.1, R412.1
unnamed: Q801.1 (B), R802.1
unnamed: K801.2, Q801.3 (C)
unnamed: Q802.1 (B), R804.1
unnamed: K802.2, Q802.3 (C)
unnamed: Q803.1 (B), R806.1
unnamed: K803.2, Q803.3 (C)
unnamed: Q804.1 (B), R808.1
unnamed: K804.2, Q804.3 (C)
unnamed: C812.1, Q805.1 (B), Q805.3 (C), Q807.1 (B), R811.1
unnamed: Q805.2 (E), R810.1
unnamed: Q806.1 (B), R809.2
unnamed: K805.2, Q806.3 (C)
unnamed: Q901.3 (D), R903.2, U902.8 (~E)
unnamed: Q901.1 (G), R902.2
unnamed: Q1001.3 (D), R1003.2, U1002.8 (~E)
unnamed: Q1001.1 (G), R1002.2
unnamed: Q1101.3 (D), R1103.2, U1102.8 (~E)
unnamed: Q1101.1 (G), R1102.2
unnamed: Q1201.3 (D), R1203.2, U1202.8 (~E)
unnamed: Q1201.1 (G), R1202.2
unnamed: Q1401.1 (B), R1401.2
unnamed: Q1402.1 (B), R1402.2
unnamed: R312.2, R313.1
unnamed: R501.1, R502.2, R506.2
unnamed: R516.2, R518.1, U505.1
unnamed: R517.2, R519.1, U505.14
unnamed: R523.2, RV501.2
unnamed: R718.1, U704.4
unnamed: R719.1, U705.4
unnamed: R720.1, U704.1
unnamed: R721.1, U705.3
unnamed: R820.2, R821.1, U802.7
unnamed: R822.2, RV801.3
unnamed: R826.1, RV801.1
unnamed: R829.2, U805.1
unnamed: R830.2, U806.1
unnamed: R832.2, R835.1
unnamed: R835.2, R836.1
unnamed: R901.2, U901.1
unnamed: R1001.2, U1001.1
unnamed: R1101.2, U1101.1
unnamed: R1201.2, U1201.1
unnamed: RN701.1 (R1.1), U709.16 (SCLK)
unnamed: RN701.2 (R2.1), U709.15 (DIN)
unnamed: RN701.3 (R3.1), U709.14 (DOUT/~DRDY)
unnamed: RN701.4 (R4.1), U709.13 (~DRDY)
unnamed: R723.1, RN702.4 (R1.2), U709.11 (START)
unnamed: RN702.3 (R2.2), U709.12 (~CS)
unnamed: R208.1, TR201.10 (C_RX)
unnamed: R209.1, TR201.15 (C_TX)
unnamed: R203.2, U201.24 (RBIAS)
unnamed: R201.2, U201.10 (RXER/PHYAD0)
unnamed: C203.1, C206.1, U201.6 (VDDCR)
unnamed: C201.1, U201.5 (XTAL1/CLKIN), Y201.2
unnamed: C204.1, U201.4 (XTAL2), Y201.1
unnamed: R303.2, U301.2 (A)
unnamed: U301.4 (Y), U302.2 (D)
unnamed: R311.1, U302.5 (Q)
unnamed: R320.1, U303.94 (BOOT0)
unnamed: C313.1, R317.1, R318.2, R319.2, U303.37 (PE7)
unnamed: C310.1, U303.12 (PH0), Y301.1
unnamed: C312.1, U303.13 (PH1), Y301.2
unnamed: C403.1, L402.2, U401.1 (VIN), U401.5 (ENA)
unnamed: C405.1, U401.4 (NR)
unnamed: C404.1, L403.2, U402.1 (VIN), U402.5 (ENA)
unnamed: C406.1, U402.4 (NR)
unnamed: R407.2, R408.1, R410.1, U403.2 (FB)
unnamed: C410.1, U403.8 (SS)
unnamed: R405.1, U403.1 (VC)
unnamed: C402.1, L401.2, L404.1, R401.1, R404.1, U403.6 (VIN)
unnamed: R401.2, R402.2, R403.1, R404.2, U403.3 (~SHDN)
unnamed: C415.1, L405.1, U404.14 (VOUT+)
unnamed: C420.1, R414.1, R415.1, U405.3 (NFB)
unnamed: C419.1, L407.2, U405.1 (SW1)
unnamed: C417.1, L406.2, L407.4, R413.1, U405.5 (VIN)
unnamed: C418.1, R413.2, U405.4 (~SHDN)
unnamed: C502.2, U502.6 (CAP/2.5V)
unnamed: C504.2, U502.3 (COMP)
unnamed: R501.2, U502.1 (FS_ADJUST)
unnamed: C514.2, L502.2, R505.2, U502.19 (IOUT)
unnamed: C513.1, L501.1, R504.1, U502.20 (IOUTB)
unnamed: C509.1, U502.2 (REFOUT)
unnamed: R507.1, U501.4, U502.11 (RESET), U503.11 (RESET)
unnamed: C503.2, U503.6 (CAP/2.5V)
unnamed: C505.2, U503.3 (COMP)
unnamed: C506.1, R503.1, U503.1 (FS_ADJUST)
unnamed: C516.2, L504.2, R509.2, U503.19 (IOUT)
unnamed: C515.1, L503.1, R508.1, U503.20 (IOUTB)
unnamed: C512.1, U503.2 (REFOUT)
unnamed: U504.4 (Y), U507.6 (~CLR)
unnamed: C519.1, L501.2, R510.1, U505.3 (+)
unnamed: R512.1, R516.1, U505.2 (-)
unnamed: R519.2, R521.1, U505.5 (+)
unnamed: R518.2, R520.1, U505.6 (-)
unnamed: R523.1, R524.1, U505.10 (+)
unnamed: RN501.3, U505.9 (-)
unnamed: C520.2, L502.1, R511.2, U505.12 (+)
unnamed: R512.2, R517.1, U505.13 (-)
unnamed: C522.1, C523.1, L505.2, R513.1, R515.1, U506.3 (+)
unnamed: R522.2, U507.1 (CLK)
unnamed: U507.2 (D), U507.3 (~Q)
unnamed: R604.2, U601.3 (+)
unnamed: C602.1, R605.1, U601.4 (-)
unnamed: R606.1, U601.5 (~DISABLE)
unnamed: R603.2, U602.1 (A0)
unnamed: R602.2, U602.14 (A1)
unnamed: R605.2, U602.6 (D)
unnamed: C602.2, R610.1, U601.1, U602.4 (S1), U603.3 (+), U604.3 (+), U605.3 (+)
unnamed: R610.2, R611.1, U602.5 (S2)
unnamed: R611.2, R612.1, U602.11 (S3)
unnamed: R612.2, R613.1, U602.10 (S4)
unnamed: R608.2, U603.4 (-)
unnamed: R607.1, U603.5 (~SD)
unnamed: R614.1, R615.1, R616.1, R618.2, U604.4 (-)
unnamed: R617.1, U604.5 (~SD)
unnamed: C614.2, R620.1, R621.1, R622.1, R623.2, U605.4 (-)
unnamed: R624.1, U605.5 (~SD)
unnamed: C707.1, R708.1, R709.1, R710.1, R711.1, R712.1, R713.1, R714.1, R715.1, U701.1, U701.4 (-)
unnamed: R707.1, U701.5 (~DISABLE)
unnamed: C705.1, R705.2, R706.1, U702.1 (-)
unnamed: U703.11 (S0), U706.4 (Y)
unnamed: U703.10 (S1), U707.4 (Y)
unnamed: U703.9 (S2), U708.4 (Y)
unnamed: R708.2, U703.13 (Y0)
unnamed: R709.2, U703.14 (Y1)
unnamed: R710.2, U703.15 (Y2)
unnamed: R711.2, U703.12 (Y3)
unnamed: R712.2, U703.1 (Y4)
unnamed: R713.2, U703.5 (Y5)
unnamed: R714.2, U703.2 (Y6)
unnamed: R715.2, U703.4 (Y7)
unnamed: U703.3 (Z), U704.3, U705.1
unnamed: C724.1, R721.2, U709.8 (AINN)
unnamed: C723.2, R720.2, U709.7 (AINP)
unnamed: C729.1, R722.2, U709.10 (AVDD)
unnamed: C726.2, L701.1, U709.1 (DVDD)
unnamed: R724.1, U709.4 (~RESET)
unnamed: R819.1, U802.2 (-)
unnamed: R820.1, U802.6 (-)
unnamed: R821.2, R823.1, R825.1, U802.10 (+)
unnamed: C815.2, C817.1, R824.1, RV801.2, U802.9 (-)
unnamed: C819.1, R831.1, U801.4, U802.12 (+)
unnamed: R825.2, U802.13 (-), U802.14
unnamed: C813.2, R818.1, U803.2 (-)
unnamed: C816.2, R827.1, U804.2 (-)
unnamed: R833.1, U807.2 (A)
unnamed: U805.2, U807.4 (Y)
unnamed: R834.1, U808.2 (A)
unnamed: U806.2, U808.4 (Y)
unnamed: R837.1, U809.2 (A)
unnamed: U801.6, U809.4 (Y)
unnamed: U901.2, U903.1
unnamed: C903.1, R904.1, U901.4, U902.2 (-)
unnamed: C906.1, R905.1, U902.5 (C)
unnamed: C903.2, C905.1, R904.2, U902.1 (FB), U902.6, U903.3
unnamed: U1001.2, U1003.1
unnamed: C1003.1, R1004.1, U1001.4, U1002.2 (-)
unnamed: C1006.1, R1005.1, U1002.5 (C)
unnamed: C1003.2, C1005.1, R1004.2, U1002.1 (FB), U1002.6, U1003.3
unnamed: U1101.2, U1103.1
unnamed: C1103.1, R1104.1, U1101.4, U1102.2 (-)
unnamed: C1106.1, R1105.1, U1102.5 (C)
unnamed: C1103.2, C1105.1, R1104.2, U1102.1 (FB), U1102.6, U1103.3
unnamed: U1201.2, U1203.1
unnamed: C1203.1, R1204.1, U1201.4, U1202.2 (-)
unnamed: C1206.1, R1205.1, U1202.5 (C)
unnamed: C1203.2, C1205.1, R1204.2, U1202.1 (FB), U1202.6, U1203.3
unnamed: R1501.2, R1502.2, U1501.3 (+)
unnamed: R1503.1, U1501.1, U1501.2 (-)
unnamed: U1501.6 (-), U1501.7
unnamed: U1501.8, U1501.9 (-)
unnamed: U1501.13 (-), U1501.14
unnamed: K1501.3, U1502.16 (O1)
unnamed: K1502.3, U1502.15 (O2)
unnamed: K1503.3, U1502.14 (O3)
unnamed: K1504.3, U1502.13 (O4)
unnamed: K1505.3, U1502.12 (O5)
unnamed: K1506.3, U1502.11 (O6)
unnamed: U1601.13 (B1), U1602.3 (VIA)
unnamed: U1601.12 (B2), U1602.4 (VIB)
unnamed: U1601.11 (B3), U1602.5 (VOC)
unnamed: R1601.2, U1601.8 (OE)
unnamed: R1602.2, R1603.1, U1603.2 (D)
unnamed: D1601.3 (K), R1603.2, R1605.1, U1603.6 (O), U1603.8 (O), U1603.11 (O)
VCCQ: C207.1, C208.1, C209.1, C210.1, C211.1, C212.1, FB201.1, RN203.5 (R4.2), RN203.6 (R3.2), RN203.7 (R2.2), RN203.8 (R1.2), TR201.2 (C_TD), TR201.7 (C_RD), U201.1 (VDD2A), U201.19 (VDD1A)
VDDA: C317.1, C318.1, FB301.1, U303.21 (VDDA)
VREF+: R317.2, R321.1, R322.1, U303.20 (VREF+)
V_BOOST: C414.1, C517.2, C810.1, C1501.1, D402.1 (K), D803.2 (A), L402.1, R306.1, R407.1, U505.4 (V+), U802.4 (V+), U1501.4 (V+)

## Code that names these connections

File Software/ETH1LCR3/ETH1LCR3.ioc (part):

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Mcu.Name=STM32H743VITx
Mcu.Package=LQFP100
Mcu.UserName=STM32H743VITx
PA0.Mode=IN16-Single-Ended
PA0.Signal=ADC1_INP16
PA1.GPIOParameters=GPIO_Speed
PA1.GPIO_Speed=GPIO_SPEED_FREQ_VERY_HIGH
PA1.Mode=RMII
PA1.Signal=ETH_REF_CLK
PA2.GPIOParameters=GPIO_Speed
PA2.GPIO_Speed=GPIO_SPEED_FREQ_VERY_HIGH
PA2.Mode=RMII
PA2.Signal=ETH_MDIO
PA3.Signal=ADCx_INP15
PA4.Signal=COMP_DAC11_group
PA5.Signal=COMP_DAC12_group
PA6.Signal=ADCx_INP3
PA7.GPIOParameters=GPIO_Speed
PA7.GPIO_Speed=GPIO_SPEED_FREQ_VERY_HIGH
PA7.Mode=RMII
PA7.Signal=ETH_CRS_DV
PB0.Signal=ADCx_INP9
PB1.Signal=ADCx_INP5
PB11.GPIOParameters=GPIO_Speed
PB11.GPIO_Speed=GPIO_SPEED_FREQ_VERY_HIGH
PB11.Mode=RMII
PB11.Signal=ETH_TX_EN
PB12.GPIOParameters=GPIO_Speed
PB12.GPIO_Speed=GPIO_SPEED_FREQ_VERY_HIGH
PB12.Mode=RMII
PB12.Signal=ETH_TXD0
PB13.GPIOParameters=GPIO_Speed
PB13.GPIO_Speed=GPIO_SPEED_FREQ_VERY_HIGH
PB13.Mode=RMII
PB13.Signal=ETH_TXD1
PB5.GPIOParameters=GPIO_Speed,PinState,GPIO_Label
PB5.GPIO_Label=EEPROM_nWP
PB5.GPIO_Speed=GPIO_SPEED_FREQ_HIGH
PB5.PinState=GPIO_PIN_SET
PB5.Signal=GPIO_Output
PB6.Mode=I2C
PB6.Signal=I2C1_SCL
PB7.Mode=I2C
PB7.Signal=I2C1_SDA
PC0.Signal=ADCx_INP10
PC1.GPIOParameters=GPIO_Speed
PC1.GPIO_Speed=GPIO_SPEED_FREQ_LOW
PC1.Mode=RMII
PC1.Signal=ETH_MDC
PC10.GPIOParameters=GPIO_Label
PC10.GPIO_Label=DDS_SCLK
PC10.Mode=Simplex_Bidirectional_Master
PC10.Signal=SPI3_SCK
PC12.GPIOParameters=GPIO_Label
PC12.GPIO_Label=DDS_SDATA
PC12.Mode=Simplex_Bidirectional_Master
PC12.Signal=SPI3_MOSI
PC4.GPIOParameters=GPIO_Speed
PC4.GPIO_Speed=GPIO_SPEED_FREQ_VERY_HIGH
PC4.Mode=RMII
PC4.Signal=ETH_RXD0
PC5.GPIOParameters=GPIO_Speed
PC5.GPIO_Speed=GPIO_SPEED_FREQ_VERY_HIGH
PC5.Mode=RMII
PC5.Signal=ETH_RXD1
PC6.GPIOParameters=PinState,GPIO_Label
PC6.GPIO_Label=LED_BLUE
PC6.PinState=GPIO_PIN_SET
PC6.Signal=GPIO_Output
PC7.GPIOParameters=PinState,GPIO_Label
PC7.GPIO_Label=LED_RED
PC7.PinState=GPIO_PIN_SET
PC7.Signal=GPIO_Output
PC8.GPIOParameters=PinState,GPIO_Label
PC8.GPIO_Label=LED_GREEN
PC8.PinState=GPIO_PIN_SET
PC8.Signal=GPIO_Output
PD0.GPIOParameters=GPIO_Label
PD0.GPIO_Label=DDS_nFSYNC2
PD0.Signal=GPXTI0
PD1.GPIOParameters=GPIO_Label
PD1.GPIO_Label=DDS_nFSYNC1
PD1.Signal=GPIO_Output
PE10.GPIOParameters=GPIO_Label
PE10.GPIO_Label=ADS_nDRDY
PE10.Signal=GPXTI10
PE11.GPIOParameters=GPIO_Label
PE11.GPIO_Label=ADS_nCS
PE11.Mode=NSS_Signal_Hard_Input
PE11.Signal=SPI4_NSS
PE12.GPIOParameters=GPIO_Label
PE12.GPIO_Label=ADS_SCLK
PE12.Mode=Full_Duplex_Master
PE12.Signal=SPI4_SCK
PE13.GPIOParameters=GPIO_Label
PE13.GPIO_Label=ADS_DOUT
PE13.Mode=Full_Duplex_Master
PE13.Signal=SPI4_MISO
PE14.GPIOParameters=GPIO_Label
PE14.GPIO_Label=ADS_DIN
PE14.Mode=Full_Duplex_Master
PE14.Signal=SPI4_MOSI
PE15.GPIOParameters=GPIO_Label
PE15.GPIO_Label=ADS_START
PE15.Signal=GPIO_Output
PE2.GPIOParameters=GPIO_Label
PE2.GPIO_Label=MCU_DEFAULT
PE2.Signal=GPIO_Input
PE7.Mode=INM
PE7.Signal=COMP2_INM
PE9.Mode=INP
PE9.Signal=COMP2_INP
PH0-OSC_IN\ (PH0).Mode=HSE-External-Oscillator
PH0-OSC_IN\ (PH0).Signal=RCC_OSC_IN
PH1-OSC_OUT\ (PH1).Mode=HSE-External-Oscillator
PH1-OSC_OUT\ (PH1).Signal=RCC_OSC_OUT
RCC.HSE_VALUE=16000000
RCC.SYSCLKFreq_VALUE=480000000
RCC.SYSCLKSource=RCC_SYSCLKSOURCE_PLLCLK
board=custom

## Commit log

2024-07-10 New LCR meter based on AU2019 https://www.elektormagazine.com/labs/remake-lcr-meter
2024-07-11 Schematic
2024-07-19 Hardware
2024-08-04 Software and hardware
2024-09-17 PCB layout
2025-03-05 Updated project to KiCAD 9
